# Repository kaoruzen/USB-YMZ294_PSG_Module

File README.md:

# USB-PSG Module (Yamaha YMZ294)

##Whats?
Yamaha YMZ294 PSG Sound LSI Controller.

##Schematic

##PCB

##Design Environment
*KiCad 4.0.2 Stable (Electronics and PCB)

*MPLAB X IDE v3.26 (PIC18F2550 Firmware)

*MPLAB C18 v3.47 Lite (PIC18F2550 Firmware)

*C# VisualStudio2015 (PC ControlSoftware)

C# Project - SMFPlay contains "SmfLite.cs" by Keijiro Takahashi. --Thanks.
[SmfLite - A minimal class library for handling standard MIDI files on Unity.](https://github.com/keijiro/smflite)

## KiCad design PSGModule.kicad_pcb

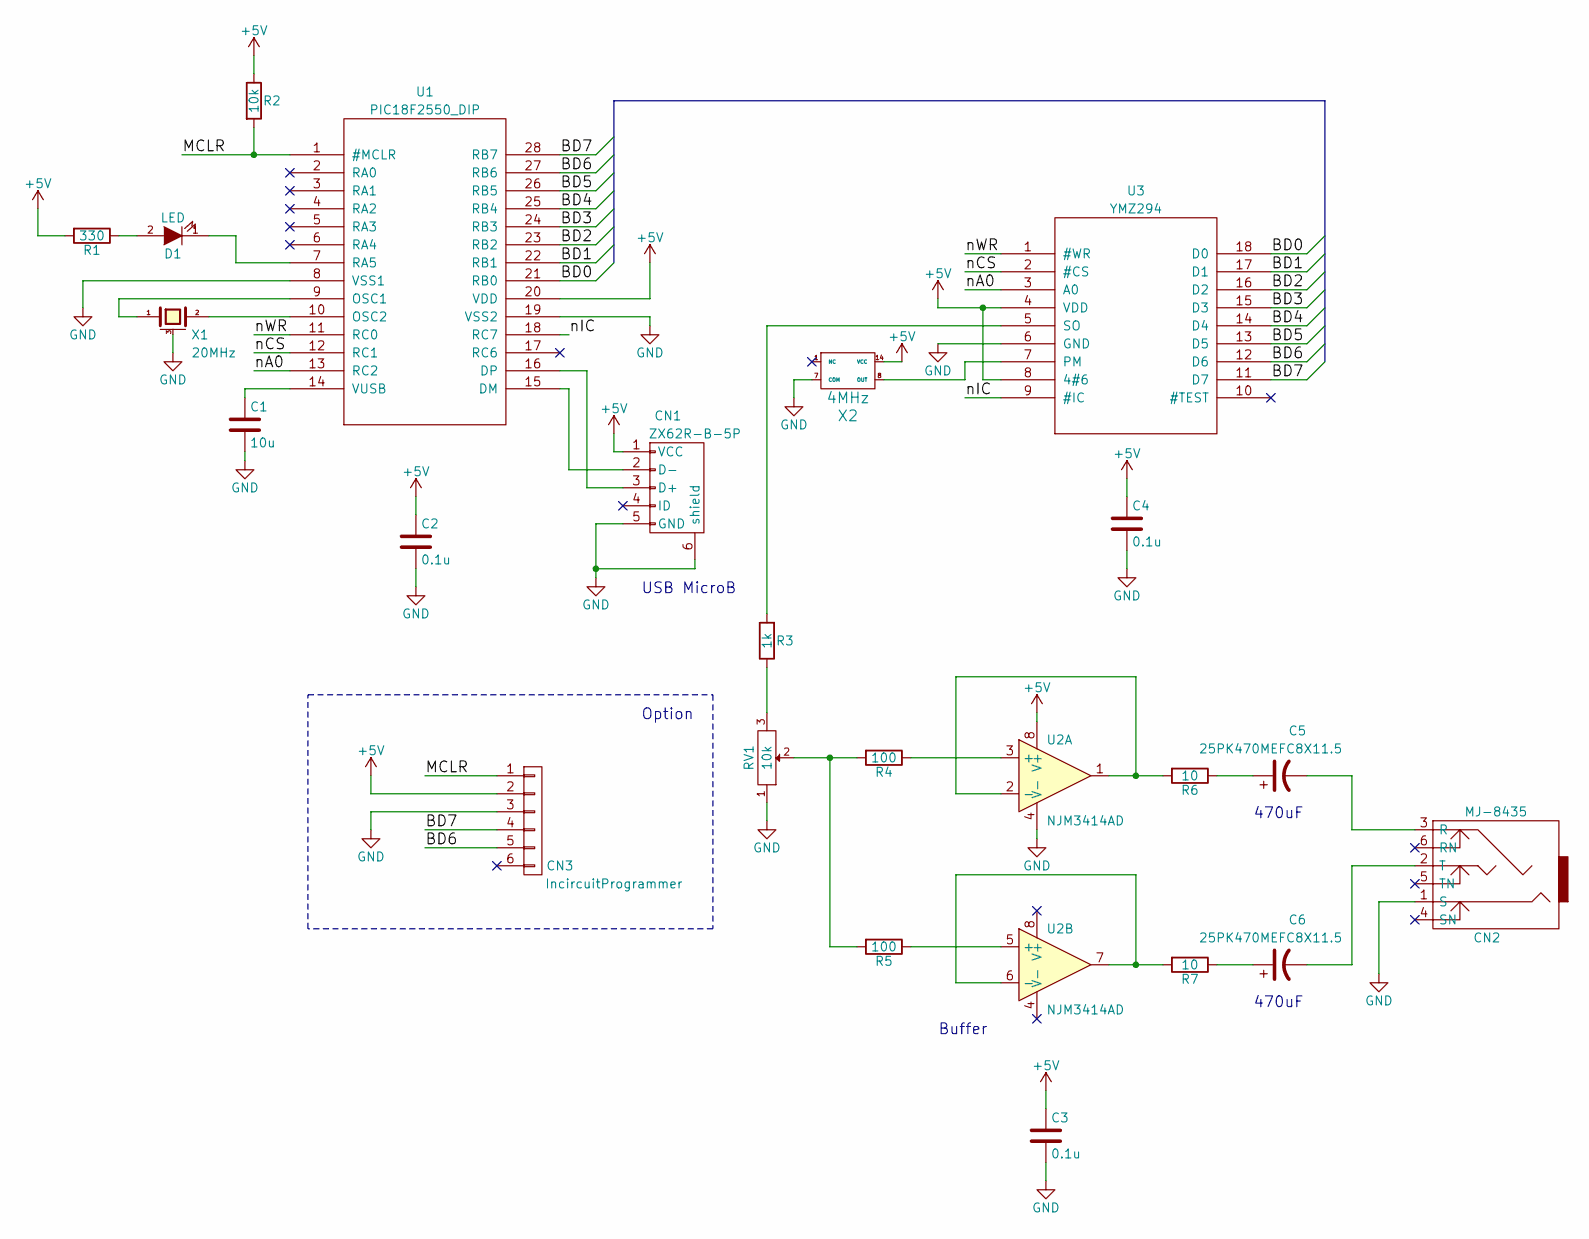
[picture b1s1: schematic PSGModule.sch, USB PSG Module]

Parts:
C1: 10u; C
C2, C3, C4: 0.1u; C
C5, C6: 25PK470MEFC8X11.5
CN1: ZX62R-B-5P
CN2: MJ-8435
CN3: IncircuitProgrammer; PINHEADER_1x6
D1: LED; LED_5mm_STD
R1: 330; R
R2: 10k; R
R3: 1k; R
R4, R5: 100; R
R6, R7: 10; R
RV1: 10k; TSR-3386
U1: PIC18F2550_DIP; PIC18F2550-I_SP
U2: NJM3414AD
U3: YMZ294
X1: 20MHz; Ceralock
X2: 4MHz; CLOCK

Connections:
+5V: C2.1, C3.1, C4.1, CN1.1 (VCC), CN3.2, R1.2, R2.1, U1.20 (VDD), U2.8 (V+), U3.4 (VDD), U3.8 (4#6), X2.14 (VCC)
/BD0: U1.21 (RB0), U3.18 (D0)
/BD1: U1.22 (RB1), U3.17 (D1)
/BD2: U1.23 (RB2), U3.16 (D2)
/BD3: U1.24 (RB3), U3.15 (D3)
/BD4: U1.25 (RB4), U3.14 (D4)
/BD5: U1.26 (RB5), U3.13 (D5)
/BD6: CN3.5, U1.27 (RB6), U3.12 (D6)
/BD7: CN3.4, U1.28 (RB7), U3.11 (D7)
/MCLR: CN3.1, R2.2, U1.1 (#MCLR)
/nA0: U1.13 (RC2), U3.3 (A0)
/nCS: U1.12 (RC1), U3.2 (#CS)
/nIC: U1.18 (RC7), U3.9 (#IC)
/nWR: U1.11 (RC0), U3.1 (#WR)
GND: C1.2, C2.2, C3.2, C4.2, CN1.5 (GND), CN1.6 (shield), CN2.1 (S), CN3.3, RV1.1, U1.8 (VSS1), U1.19 (VSS2), U2.4 (V-), U3.6 (GND), X1.3 (case), X2.7 (COM)
unnamed: C1.1, U1.14 (VUSB)
unnamed: C5.1, R6.1
unnamed: C5.2, CN2.3 (R)
unnamed: C6.1, R7.1
unnamed: C6.2, CN2.2 (T)
unnamed: CN1.2 (D-), U1.15 (DM)
unnamed: CN1.3 (D+), U1.16 (DP)
unnamed: D1.1 (K), U1.7 (RA5)
unnamed: D1.2 (A), R1.1
unnamed: R3.1, RV1.3
unnamed: R3.2, U3.5 (SO)
unnamed: R4.1, U2.3 (+)
unnamed: R4.2, R5.2, RV1.2
unnamed: R5.1, U2.5 (+)
unnamed: R6.2, U2.1, U2.2 (-)
unnamed: R7.2, U2.6 (-), U2.7
unnamed: U1.9 (OSC1), X1.1
unnamed: U1.10 (OSC2), X1.2
unnamed: U3.7 (PM), X2.8 (OUT)

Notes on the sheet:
Buffer
Option
470uF
USB MicroB

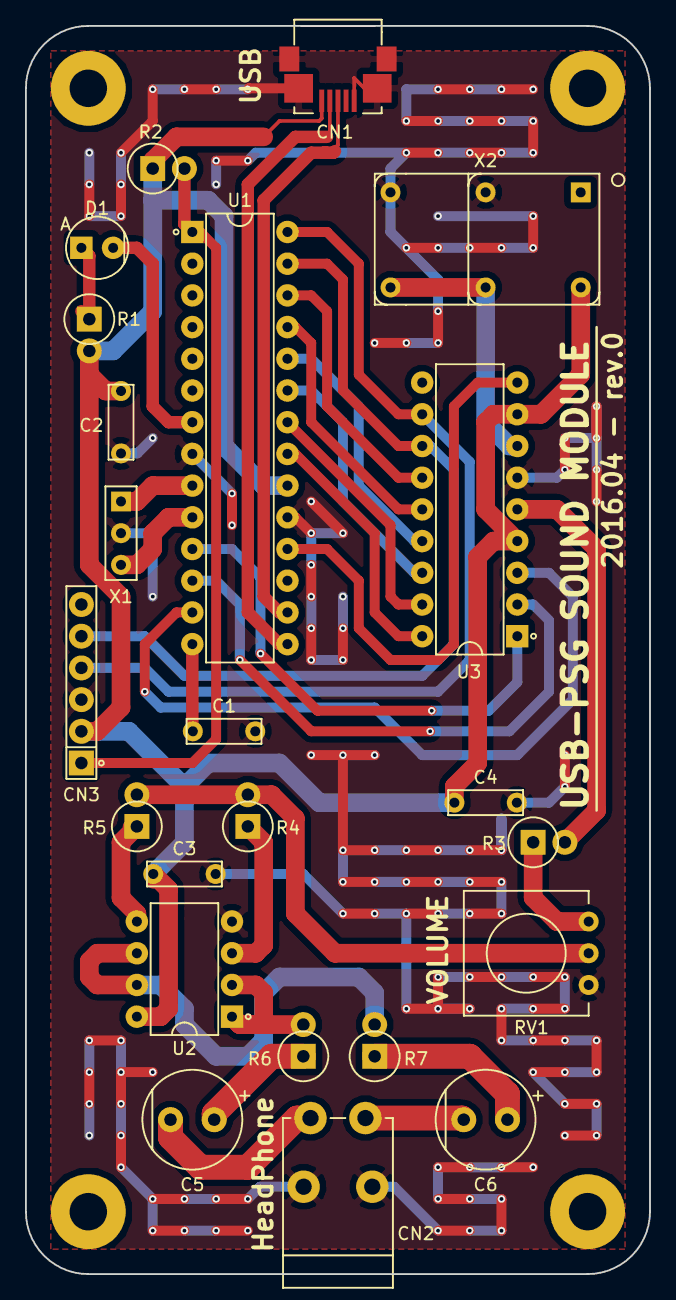
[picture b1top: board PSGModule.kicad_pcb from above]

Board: 2 copper layers, 50.0 x 100.0 mm, 23 parts (0 on the bottom side), 34 nets.

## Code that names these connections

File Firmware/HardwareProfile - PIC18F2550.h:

/********************************************************************
 FileName:      HardwareProfile - PIC24F Starter Kit.h
 Dependencies:  See INCLUDES section
 Processor:     PIC18F2550
 Hardware:      KZEN-AVRWriter
 Compiler:      Microchip C18
 Company:       Microchip Technology, Inc.

 Software License Agreement:

 The software supplied herewith by Microchip Technology Incorporated
 (the �Company�E for its PIC� Microcontroller is intended and
 supplied to you, the Company�s customer, for use solely and
 exclusively on Microchip PIC Microcontroller products. The
 software is owned by the Company and/or its supplier, and is
 protected under applicable copyright laws. All rights are reserved.
 Any use in violation of the foregoing restrictions may subject the
 user to criminal sanctions under applicable laws, as well as to
 civil liability for the breach of the terms and conditions of this
 license.

 THIS SOFTWARE IS PROVIDED IN AN �AS IS�ECONDITION. NO WARRANTIES,
 WHETHER EXPRESS, IMPLIED OR STATUTORY, INCLUDING, BUT NOT LIMITED
 TO, IMPLIED WARRANTIES OF MERCHANTABILITY AND FITNESS FOR A
 PARTICULAR PURPOSE APPLY TO THIS SOFTWARE. THE COMPANY SHALL NOT,
 IN ANY CIRCUMSTANCES, BE LIABLE FOR SPECIAL, INCIDENTAL OR
 CONSEQUENTIAL DAMAGES, FOR ANY REASON WHATSOEVER.

********************************************************************
 File Description:

 Change History:
  Rev   Date         Description
  1.0   11/19/2004   Initial release
  2.1   02/26/2007   Updated for simplicity and to use common
                     coding style
  2.3   09/15/2008   Broke out each hardware platform into its own
                     "HardwareProfile - xxx.h" file
********************************************************************/

#ifndef HARDWARE_PROFILE_PSGMOD_PIC18F2550
#define HARDWARE_PROFILE_PSGMOD_PIC18F2550


    /*******************************************************************/
    /******** USB stack hardware selection options *********************/
    /*******************************************************************/
    // Self-Power Only Device

    //#define USE_SELF_POWER_SENSE_IO
    //#define tris_self_power     TRISCbits.TRISC2
    #define self_power          0

 //   #define USE_USB_BUS_SENSE_IO
//    #define tris_usb_bus_sense  TRISBbits.TRISB3      // Assign VBUS to RB3
    #define USB_BUS_SENSE       PORTBbits.RB3


    //Uncomment this to make the output HEX of this project 
    //   to be able to be bootloaded using the HID bootloader
    //#define PROGRAMMABLE_WITH_USB_HID_BOOTLOADER	

    //If the application is going to be used with the HID bootloader
    //  then this will provide a function for the application to 
    //  enter the bootloader from the application (optional)
    #if defined(PROGRAMMABLE_WITH_USB_HID_BOOTLOADER)
        #define EnterBootloader() __asm__("goto 0x400")
    #endif   

    /** Board definition ***********************************************/
    //These defintions will tell the main() function which board is
    //  currently selected.  This will allow the application to add
    //  the correct configuration bits as wells use the correct
    //  initialization functions for the board.  These defitions are only
    //  required in the stack provided demos.  They are not required in
    //  final application design.
    #define CLOCK_FREQ 48000000
    #define GetSystemClock() CLOCK_FREQ


    /*******************************************************************/
    /*******************************************************************/
    /*******************************************************************/
    /******** Application specific definitions *************************/
    /*******************************************************************/
    /*******************************************************************/
    /*******************************************************************/

    /** Board definition ***********************************************/
    //These defintions will tell the main() function which board is
    //  currently selected.  This will allow the application to add
    //  the correct configuration bits as wells use the correct
    //  initialization functions for the board.  These defitions are only
    //  required in the stack provided demos.  They are not required in
    //  final application design.
    #define PSGMOD_PIC18F2550


    #define LED PORTAbits.RA5

    #define WR PORTCbits.RC0
    #define CS PORTCbits.RC1
    #define A0 PORTCbits.RC2
    #define IC PORTCbits.RC7
    #define BUS PORTB


    #define FIRMWARE_VER    "V,REL20150422\r\n"


#endif  //HARDWARE_PROFILE_PIC24F_STARTER_KIT_H

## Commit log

2017-02-11 :lollipop: Added .gitattributes & .gitignore files
2017-02-11 Designed PCB
2017-02-11 Add PC Control Software
